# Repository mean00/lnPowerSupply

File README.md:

# lnPowerSupply
## Introduction
This is a very overengineered desktop power supply.
Small feature list :
- Powered by Lidl or Aldi battery back
- Current limiting (not very good)
- Large display (320x240)
- Large fonts 

## C++ vs Rust
The software comes in two flavors :
- C++
- Rust 

You can switch to either one (un)commenting the _SET(ENABLE_RUST True)_ in the top CmakeLists.txt

NB: The rust version contains bit of c++ (the lnArduino low level driver + the ina219 driver)

## Electrical Detail

You can use pretty much any DC/DC converter as a core, you need to adjust R2 depending on the feedback voltage
(see lnPowerSupply.pdf)
Be careful to stay below ~ 24v else the INA219 will blow.

Formula is ~ R2>420*FB 
 * FB=1.25=> R2>500
 * FB=0.8=>  R2>360...

The overal design is made of 3 parts :
- The DC/DC converter board itself
- The DC/DC control board, controlled over i2C
- The main board with a STM32 or GD32 driving the screen

## Why go to such a design ?
You need to have the control part close to the DC/DC
You need to have the SPI screen AWAY from the control board

[Small Youtube demo ](https://youtu.be/UPAjdyqt5LI)

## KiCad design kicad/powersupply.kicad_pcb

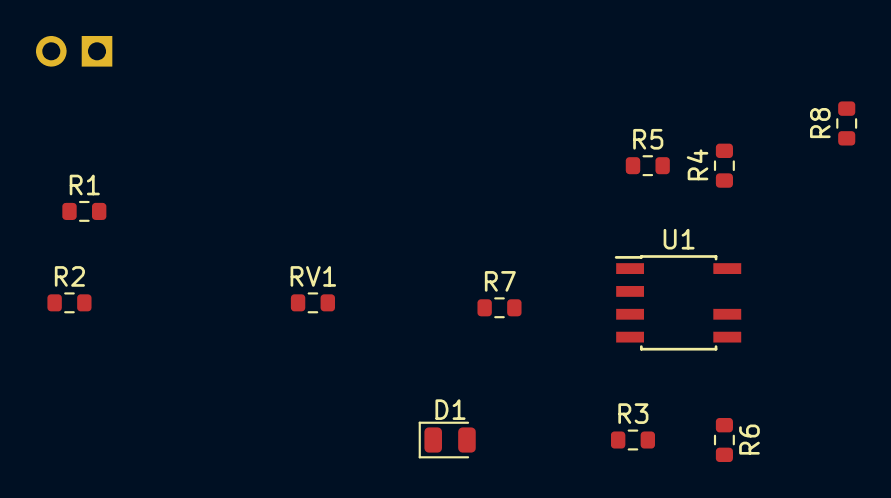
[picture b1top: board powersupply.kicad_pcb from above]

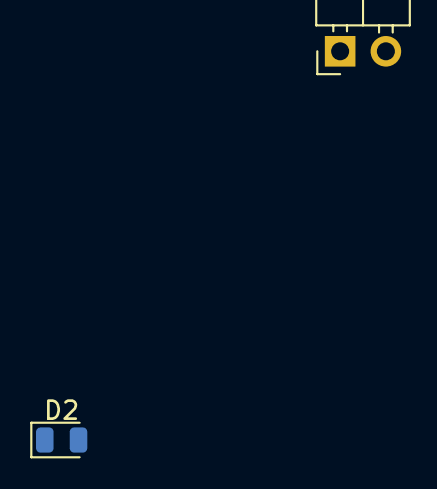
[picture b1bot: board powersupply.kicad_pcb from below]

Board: 2 copper layers, 13 parts (2 on the bottom side), 10 nets, no tracks yet.

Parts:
D1, D2: D_Schottky; D_0805_2012Metric
J1: Conn_01x02_Female; PinHeader_1x02_P2.54mm_Horizontal
R1: 10m; R_0603_1608Metric
R2: 3.3k; R_0603_1608Metric
R3: 1k; R_0603_1608Metric
R4, R6, R8: 50k; R_0603_1608Metric
R5, R7: 1K; R_0603_1608Metric
RV1: 100k; R_0603_1608Metric
U1: LM358; SOIC-8-N7_3.9x4.9mm_P1.27mm

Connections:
GND: R1.2, R2.2, R3.2, R6.2
unnamed: D1.1 (K), D2.1 (K)
unnamed: D1.2 (A), R8.2
unnamed: D2.2 (A), R2.1
unnamed: J1.1, RV1.1, RV1.2
unnamed: J1.2, R1.1, U1.3 (+)
unnamed: R3.1, R4.1, U1.2 (-)
unnamed: R4.2, R5.1, U1.1
unnamed: R5.2, R6.1, U1.5 (+)
unnamed: R7.1, R8.1, U1.6 (-)

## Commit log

2022-07-16 skeleton
2022-08-11 sort of basic version
2022-08-11 update lnArduino
2022-08-13 basic power supply
2022-08-13 take wires resistance into account
2022-08-14 mostly complete skeleton
2022-08-14 holdoff enable/disable output for a bit
2022-08-14 add schematic
2022-08-14 add screenshot
2022-08-14 update readm
2022-08-14 cleanup the code a bit
2022-08-14 and more clenanup
2022-08-14 constify pins
2022-08-14 pick only the glyphs we use
2022-08-14 fix typo
2022-08-15 change display a bit, add power
2022-08-15 update ili
2022-08-15 add additional glyphs, redo display a bit, switch to semi signaled based refresh
2022-08-15 add internal screenshot
2022-08-16 update PDF
2022-08-16 annotate components
2022-08-17 add a small screen benchmark + enable the ILI internal cache
2022-08-18 add dummy rust payload
2022-08-20 unsafe everything
2022-08-20 rename app to rnPowerSupply.rs
2022-08-20 prepare for LTO
2022-08-20 do some stuff in the rust part
2022-08-21 rust continued
2022-08-21 more c++/rust glue
2022-08-21 remove the whole rust part if LN_ENABLE_RUST is not set
2022-08-21 remove warnings
2022-08-22 resync
2022-08-24 first callback hook
2022-08-24 reuse the &runtime ref for both callbacks
2022-08-24 move allocated to rnArduino + remove some warnings
2022-08-31 update rsArduino to remove panic + use s profile to shrink size
2022-09-01 use a smaller C++ bootstrap code when using rust
2022-09-01 add lnBMP freertos debug hooks
2022-09-01 add bindgen script
2022-09-03 by default rust is disabled + update kicad
2022-09-03 dont double initialize the i2c task, have low bat threshold higer, remove dead code
2022-09-03 enable rust
2022-09-08 use rustified enum
2022-09-10 switch to clang, cleanup bindgen stuff
2022-09-10 sync lnArduino
2022-09-10 lnArduino
2022-09-10 switch to rn instead of ln
2022-09-17 update font and convert script
2022-09-17 update externals
2022-09-18 use intermediate safe binding
2022-09-18 use binding, continued
2022-09-20 build fully with clang
2022-09-27 fix build of C version
2022-09-30 sync lnArduino + update llvm
2022-10-08 cleanup
2022-10-09 some vscode settings
2022-10-09 small cleanup (cosmetic)
2022-10-09 sort of fix uint8_t
2022-10-25 begin switching to rust ILI
2022-11-01 sync
2022-11-05 begin display in rust
2022-11-05 begin displaying info
2022-11-05 mostly complete display
2022-11-05 fix printout
2022-11-05 use the new trait
2022-11-05 mostly feature complete
2022-11-05 sync simplerILI
2022-11-05 update fonts
2022-11-05 increment holdoff + update readme
2022-12-11 switch to simpler_gfx font
2022-12-15 split cpp and rs apart
2022-12-16 mcp4725 and ina219
2022-12-16 most of the ina219 code
2022-12-16 export compile.json
2022-12-16 cleanup ina219
2022-12-16 cleanup before jumping
2022-12-16 shuffle stuff around
2022-12-17 pcf8574
2022-12-17 PC8754 working
2022-12-17 ina219 test code
2022-12-18 workish ina219, not great accuracy though
2022-12-18 add task to rust bindings
2022-12-18 link to c_binding
2022-12-18 basic skeleton
2022-12-18 flesh out i2c task
2022-12-18 implement lifetime
2022-12-19 re-activate some app code inside taist.rs + remove warnings
2022-12-20 almost complete app
2022-12-20 almost there
2022-12-22 remove unneeded cpp files
2022-12-22 not working
2022-12-22 use a void* to avoid endless headache
2022-12-23 use dirty c callback to avoid over complicated proper fix
2022-12-23 cleanup the rs part, we dont need those C++ libs in that case
2022-12-23 switch off lto through rust cflags
2022-12-24 working ina219, fix i2c error
2022-12-24 display a small battery icon to warn we are going low
2022-12-24 add battery icons
2022-12-25 update ILI9341
2022-12-25 avoit the front LED flashing at start
2022-12-25 run clippy
2022-12-26 rename rust binding
2023-01-21 update simplerILI9341
2023-02-06 use gfx_display module
2023-02-06 update lnArduino / ili9341 to get new widgets
2023-02-06 remove warning due to non mainline feature(default_alloc_error_handler)
2023-02-06 ili : take gauge fix
2023-02-06 sync simplerILI9341
2023-02-07 rust: remove reference to old ili::gauge
2023-02-07 rust : re enable lto
2023-02-07 sync ili
2023-02-08 arm: update to clang17
2023-02-22 use relative url for submodules
2023-06-24 vscode : update settings and launch
2023-06-24 C++ version : i2c task explicitely set the stack size to 1024 and avoid stack overflow
2023-06-24 rust : also explicetly set stack size to 1024 (as it was before for the rust version)
2023-06-24 build: re-enable C version for testing purpose
2023-10-29 update to newer lnArduino + rust binding
2024-05-05 disable lto optimzation
2024-05-05 use regular RUST_ADD macro
2024-05-05 update submodule path
2024-05-05 update to newer simplerILI+ lnArduino
2024-05-05 clang-tidy / clang-format
2024-05-05 partial update to newer rust binding
2024-05-07 rn: update timing_adc
2024-05-08 update kicad
2024-05-08 debug:move uart to uart1, not uart0
2024-05-08 clippy
2024-05-08 update lnArduino + add C hook to ease debug
2024-05-08 fix sim
2024-05-09 cargo fmt
2025-02-23 update to recent mcuSelect/platform / lnarduino / ili
2025-02-25 slight update on sim
2025-02-28 gfx: dont reuse the gauge for both displays, that makes the internal caching act silly
2025-03-01 increase initial stack
2025-03-01 update ili driver
2025-10-03 Update for newer esprit, add devcontainer
2025-10-03 update simplerILI
2025-10-04 clippy + gitignore
2025-10-22 update kicad schematic with latched button
2025-10-22 update esprit
2025-10-22 switch to rtt logging
2025-10-22 update mcuselect with bluepill settings
2025-10-22 switch to latched button
2025-10-22 lower debounce to 40ms x2
2025-10-22 rename to ButtonEvent as it is used both for on and off
2025-10-26 complete schematic
2025-10-28 update esprit to get newer i2c driver, use GD32F3 as default
2025-10-28 remove old cpp impl
2025-10-28 button is a pullup, not a pulldown
2025-10-31 update esprit to get the updated i2c driver
